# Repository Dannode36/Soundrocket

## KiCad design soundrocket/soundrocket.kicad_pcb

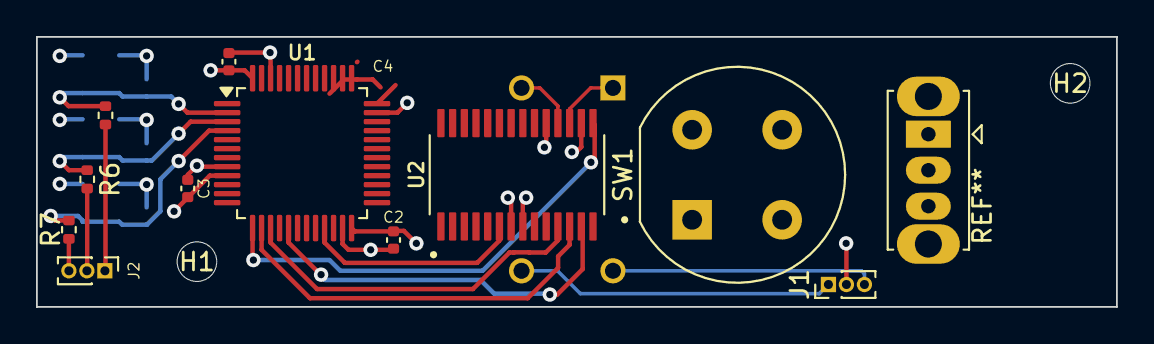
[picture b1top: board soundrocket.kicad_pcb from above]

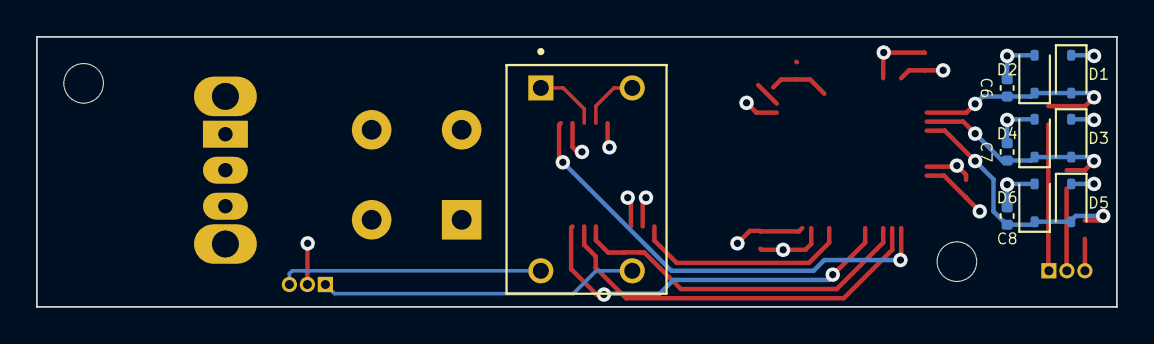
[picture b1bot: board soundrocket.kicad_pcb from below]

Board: 4 copper layers, 60.0 x 15.0 mm, 23 parts (10 on the bottom side), 18 nets.

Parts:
C2, C3, C4: C_Small; C_0402_1005Metric
C6, C7, C8: 10nF; C_0402_1005Metric
D1, D2, D3, D4, D5, D6: Schottky; D_SOD-323
H1, H2: MountingHole; MountingHole_2.2mm_M2
J1: XLR_OUT_1x3; PinHeader_1x03_P1.00mm_Vertical
J2: XLR_IN_1x3; PinHeader_1x03_P1.00mm_Vertical
R5, R6, R7: 200K; R_0402_1005Metric
SW1: SW_Push; SW_D6_C_90
T1: PE-65612NL; XFMR_PE-65612NL
U1: STM32F410CBTx; LQFP-48_7x7mm_P0.5mm
U2: DIT4192IPW; SOP65P640X120-28N

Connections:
3V3: C2.1, C3.2, C4.1, D1.1 (K), D3.1 (K), D5.1 (K), U1.9 (VDDA), U1.24 (VDD), U1.36 (VDD), U1.48 (VDD), U2.7 (V_IO)
/XLR-TX+: J1.1, T1.4
/XLR-TX-: J1.3, T1.3
GND: C2.2, C3.1, C4.2, C6.2, C7.2, C8.2, D2.2 (A), D4.2 (A), D6.2 (A), J1.2, SW1.1, U1.8 (VSSA), U1.23 (VSS), U1.35 (VSS), U1.46 (VSS), U2.8 (DGND), U2.16 (DGND-1)
IO_XLR_IN1: C6.1, D1.2 (A), D2.1 (K), R5.2, U1.2 (PC13)
IO_XLR_IN2: C7.1, D3.2 (A), D4.1 (K), R6.2, U1.3 (PC14)
IO_XLR_IN3: C8.1, D5.2 (A), D6.1 (K), R7.2, U1.4 (PC15)
MCLK: U1.21 (PB10), U2.6 (MCLK)
RST: U1.13 (PA3), U2.15 (RST)
SCLK: U1.15 (PA5), U2.11 (SCLK)
SDATA: U1.17 (PA7), U2.13 (SDATA)
SW1: SW1.2, U1.25 (PB12)
TX+: T1.2, U2.18 (TX+)
TX-: T1.1, U2.17 (TX-)
WS: U1.14 (PA4), U2.12 (SYNC)
XLR_IN1: J2.1, R5.1
XLR_IN2: J2.2, R6.1
XLR_IN3: J2.3, R7.1

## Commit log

2025-07-13 Changed to dt4192
2025-07-27 work
2025-08-01 schematic start
2025-08-03 Getting close to final
2025-08-04 Removed /5V0 net
2025-08-08 shrink
2025-08-08 soundbullet format
2025-08-08 compact version complete
2025-08-10 Gerbers
2025-08-15 Hardware Test & Revision 2
2025-08-21 Adjusted silkscreen labels
2025-08-21 Updated Gerbers
2025-08-23 Prototype Revision 2
2025-08-24 Blend File
2025-08-24 Case Model
2025-08-24 Fixed 3d print export on shell model
2025-08-25 stm32 running out of space
